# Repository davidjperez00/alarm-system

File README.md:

# alarm-system

## Host Machine Setup

### WSL Install
1. Open powershell as administrator and run (Project Version):
```wsl --intall```

### WSL Connect Serial Ports From Windows
1. When we setup esp idf project build system we will have to connect our Windows usb serial ports to our WSL operation system.
```winget install usbipd ```
2. RESTART your pc, <b>This is only a one time process</b>, once you set
this up it will connect the port service on all boots?
3. After the reboot, In a Powershell window, connect the windows usb port to a WSL port. <b>You will need to do this every reboot</b>. 
</r>TODO: consider connecting the port and through windows only? 

In Powershell admin terminal, look for device Connected to Windows machine: 
```
usbipd list
```

5.  Bind port to WSL OS, Example: 7-1
```
usbipd bind --busid <BUSID>
usbipd attach --wsl --busid <BUSID>
```
6. Back in wsl windows you should see new device connected:
```
# New device should appear in list
ls /dev/tty*
```
7. Then, again in WSL terminal Give current user permission to access port: (TODO: might only need to do once.)
```
sudo usermod -a -G dialout $USER
```

### Github SSH Key Setup for WSL
1. In WSL create keys:
```ssh-keygen -t ed25519 -C "your_email@example.com"```
2. Create directory and manage permissions (Optional), replace <ssh_private_key> with private key name from last step.
```
# Create ssh directory
install -d ~/.ssh
chmod 700 ~/.ssh
# Move private key to ssh directory and set permissions
mv <ssh_private_key>
chmod 600 <ssh_private_key>
```
3. Start ssh agent to add ssh key to working memory (avoids having to specify the key with "ssh -i")
```
# launch ssh-agent
eval "$(ssh-agent -s)"
# Add the key to the agent
ssh-add ~/.ssh/<ssh_private_key>
```

### Required Software Setup 
1. Run the following to install all required software for building this project:
```
./host_dependencies_setup.sh
```

### Building and Running Project
1. Setup esp-idf environemnt variables by running (Only required ONCE when new terminal is opened):
```
source $IDF_PATH/export.sh
```
1. 1 (Optional) Add it to bash profile to load everytime bash terminal window is launched
```
echo "source $IDF_PATH/export.sh" >> ~/.bashrc
```
2. Setting our own ports environment variables?
```
TODO: implemement and test this:
export IDF_TARGET=esp32
export ESPPORT=
export ESPBAUD=
```

3. Building from <b>Src/blink</b>
```
idf.py build
```

4. 

5. Flashing to Device
```
idf.py flash 
```

# Improving Build Speed

## 1. Removing unused config

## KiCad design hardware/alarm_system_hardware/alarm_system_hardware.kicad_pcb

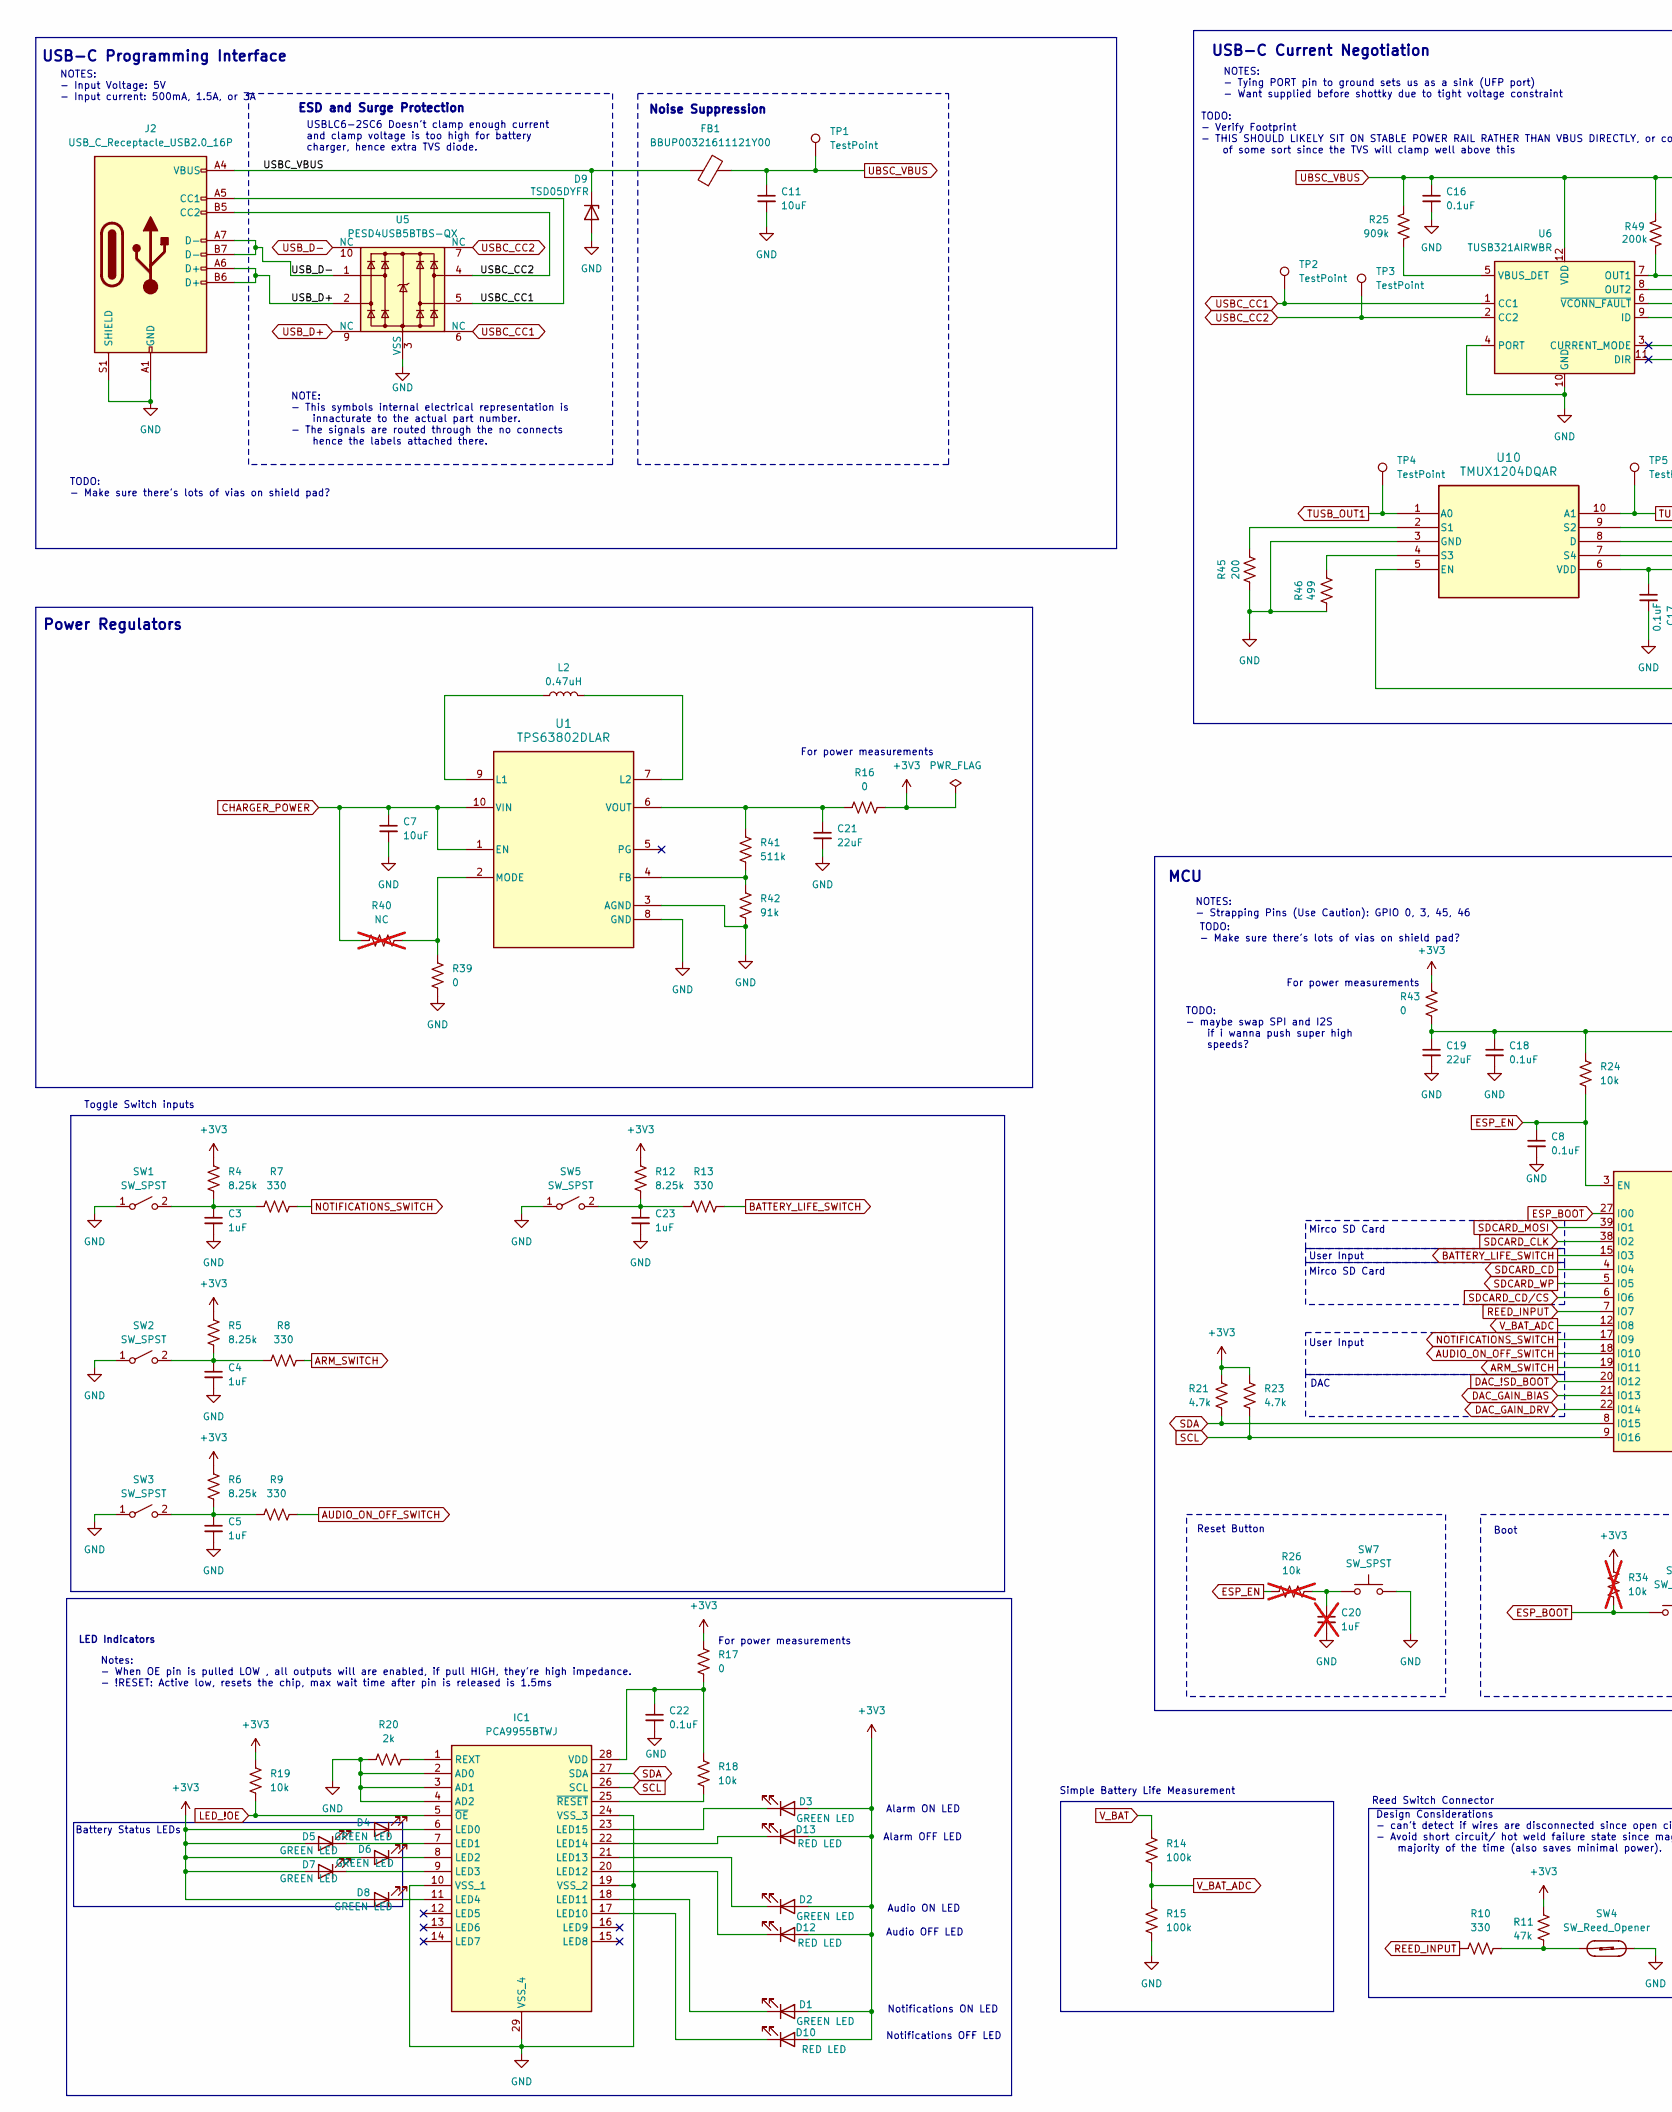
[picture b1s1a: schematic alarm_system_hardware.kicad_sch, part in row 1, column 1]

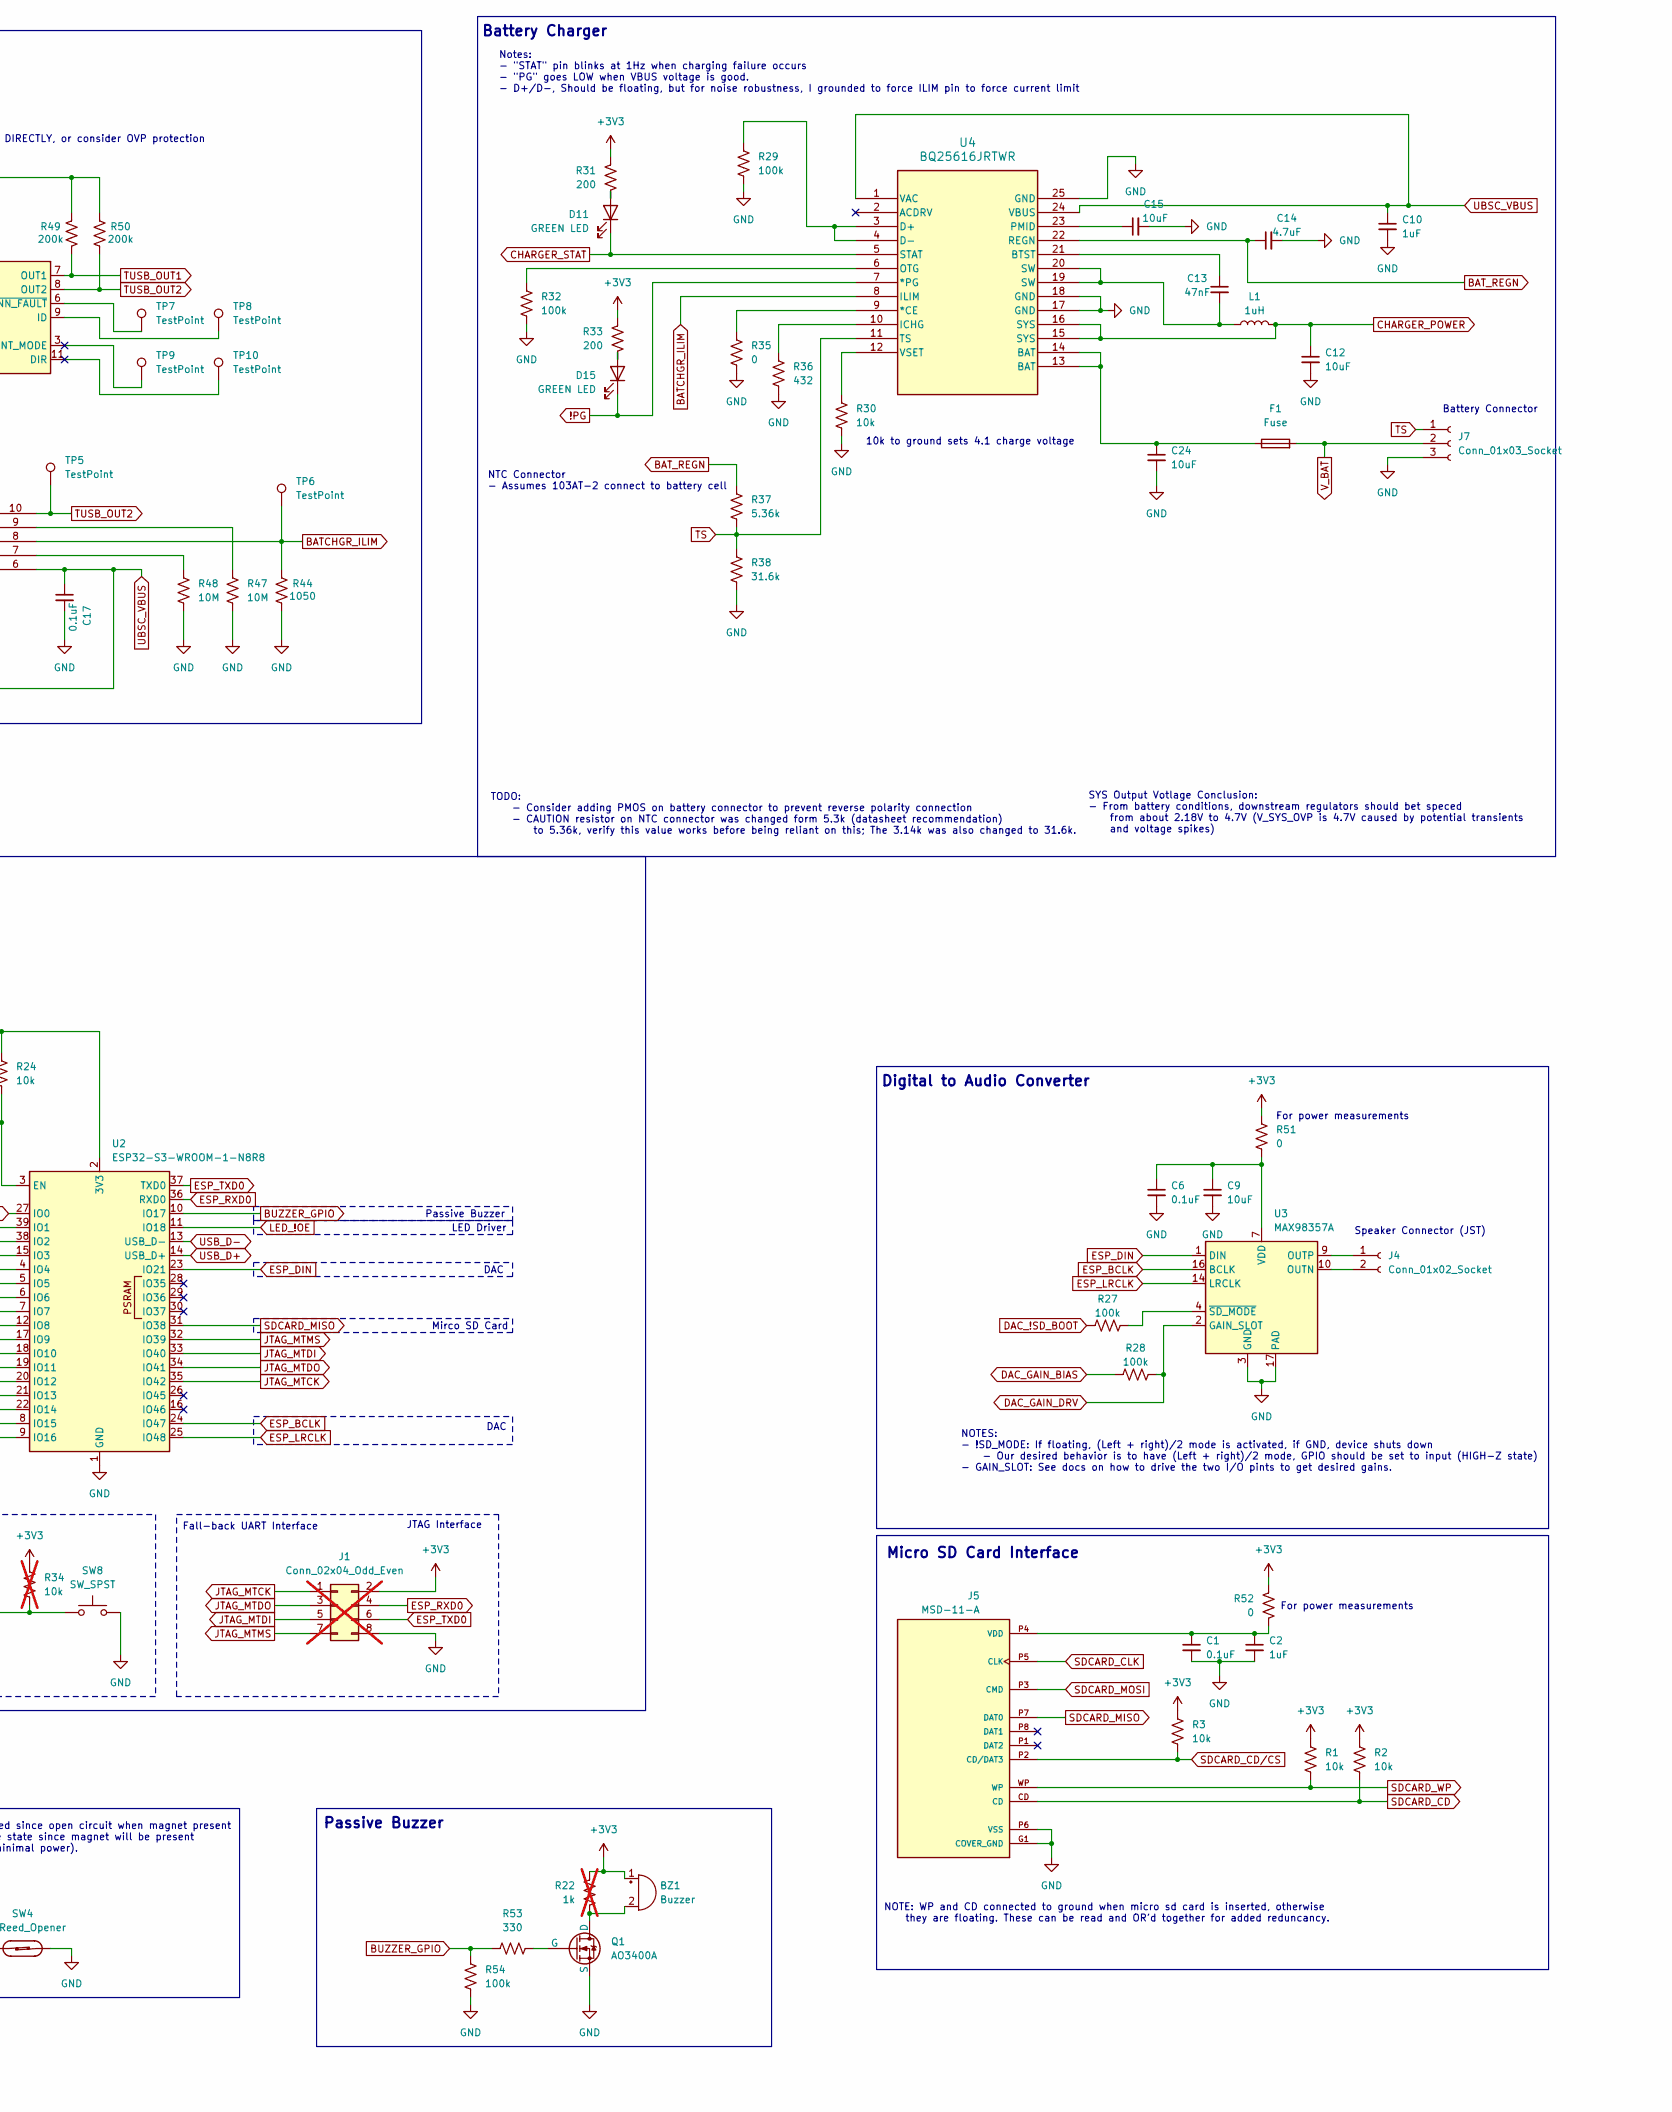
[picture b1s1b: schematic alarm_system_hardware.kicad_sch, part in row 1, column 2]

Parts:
BZ1: Buzzer; PS1440P02BT_TDK; Manufacturer_Part_Number PS1440P02BT
C1, C6, C8, C16, C17, C18, C22: 0.1uF; C_0805_2012Metric_Pad1.18x1.45mm_HandSolder; Manufacturer_Part_Number CC0805KRX7R9BB104
C2, C3, C4, C5, C10, C23: 1uF; C_0805_2012Metric_Pad1.18x1.45mm_HandSolder; Manufacturer_Part_Number GRM21BR71C105KA01L
C7, C9, C11, C12, C15, C24: 10uF; C_0805_2012Metric_Pad1.18x1.45mm_HandSolder; Manufacturer_Part_Number GRM21BR71A106KA73L
C13: 47nF; C_0805_2012Metric_Pad1.18x1.45mm_HandSolder; Manufacturer_Part_Number CL21B473KBCNNNC
C14: 4.7uF; C_0805_2012Metric_Pad1.18x1.45mm_HandSolder; Manufacturer_Part_Number CL21B473KBCNNNC
C19, C21: 22uF; C_0805_2012Metric_Pad1.18x1.45mm_HandSolder; Manufacturer_Part_Number GRM21BZ71A226ME15L
C20: 1uF; C_0805_2012Metric_Pad1.18x1.45mm_HandSolder; Manufacturer_Part_Number GRM21BR71C105KA01L; not fitted
D1, D2, D3, D4, D5, D6, D7, D8, D11, D15: GREEN LED; LED_0805_2012Metric; Manufacturer_Part_Number LTST-C171KGKT
D9: TSD05DYFR; D_SOD-323_HandSoldering; Manufacturer_Part_Number TSD05DYFR
D10, D12, D13: RED LED; LED_0805_2012Metric; Manufacturer_Part_Number LTST-C171KRKT
F1: Fuse; Fuse_0805_2012Metric; Manufacturer_Part_Number MFU0805FF03000P500
FB1: BBUP00321611121Y00; R_1206_3216Metric_Pad1.30x1.75mm_HandSolder; Manufacturer_Part_Number BBUP00321611121Y00
IC1: PCA9955BTWJ; SOP65P640X110-29N; Manufacturer_Part_Number PCA9955BTWJ; Mouser Part Number 771-PCA9955BTW
J1: Conn_02x04_Odd_Even; PinHeader_2x04_P2.54mm_Vertical; not fitted
J2: USB_C_Receptacle_USB2.0_16P; SAMESKY_UJ20-C-H-G-SMT-1-P16-TR; Manufacturer_Part_Number UJ20-C-H-G-SMT-1-P16-TR
J4: Conn_01x02_Socket; CONN_S2B-PH-K-S_JST; Manufacturer_Part_Number S2B-PH-K-S
J5: MSD-11-A; CUI_MSD-11-A; PARTREV 1.02; DigiKey_Part_Number 2223-MSD-11-ACT-ND
J7: Conn_01x03_Socket; TerminalBlock_Phoenix_PT-1,5-3-5.0-H_1x03_P5.00mm_Horizontal; Manufacturer_Part_Number 1935174
L1: 1uH; IND_VLS5045EX-1R0N; Manufacturer_Part_Number VLS5045EX-1R0N
L2: 0.47uH; IND_IHLP-2020CZ-L; Manufacturer_Part_Number IHLP2020CZERR47M11; LCSC Part # C5298158
Q1: AO3400A; SOT-23-3; Manufacturer_Part_Number AO3400A
R1, R2, R3, R18, R19, R24, R30: 10k; R_0805_2012Metric_Pad1.20x1.40mm_HandSolder; Manufacturer_Part_Number RMCF0805FT10K0
R4, R5, R6, R12: 8.25k; R_0805_2012Metric_Pad1.20x1.40mm_HandSolder; Manufacturer_Part_Number RT0805BRD078K25L
R7, R8, R9, R10, R13, R53: 330; R_0805_2012Metric_Pad1.20x1.40mm_HandSolder; Manufacturer_Part_Number RC0805JR-07330RL
R11: 47k; R_0805_2012Metric_Pad1.20x1.40mm_HandSolder; Manufacturer_Part_Number RC0805FR-0747KL
R14, R15, R27, R28, R29, R32, R54: 100k; R_0805_2012Metric_Pad1.20x1.40mm_HandSolder; Manufacturer_Part_Number RC0805FR-07100KL
R16, R17, R35, R39, R43, R51, R52: 0; R_0805_2012Metric_Pad1.20x1.40mm_HandSolder; Manufacturer_Part_Number RC0805JR-070RL
R20: 2k; R_0805_2012Metric_Pad1.20x1.40mm_HandSolder; Manufacturer_Part_Number RC0805FR-072KL
R21, R23: 4.7k; R_0805_2012Metric_Pad1.20x1.40mm_HandSolder; Manufacturer_Part_Number RC0805FR-074K7L
R22: 1k; R_0805_2012Metric_Pad1.20x1.40mm_HandSolder; not fitted
R25: 909k; R_0805_2012Metric_Pad1.20x1.40mm_HandSolder; Manufacturer_Part_Number RC0805FR-07909KL
R26, R34: 10k; R_0805_2012Metric_Pad1.20x1.40mm_HandSolder; Manufacturer_Part_Number RMCF0805FT10K0; not fitted
R31, R33, R45: 200; R_0805_2012Metric_Pad1.20x1.40mm_HandSolder; Manufacturer_Part_Number RC0805FR-07200RL
R36: 432; R_0805_2012Metric_Pad1.20x1.40mm_HandSolder; Manufacturer_Part_Number RC0805FR-07432RL
R37: 5.36k; R_0805_2012Metric_Pad1.20x1.40mm_HandSolder; Manufacturer_Part_Number CRCW08055K36FKEA
R38: 31.6k; R_0805_2012Metric_Pad1.20x1.40mm_HandSolder; Manufacturer_Part_Number RC0805FR-0731K6L
R40: NC; R_0805_2012Metric_Pad1.20x1.40mm_HandSolder; not fitted
R41: 511k; R_0805_2012Metric_Pad1.20x1.40mm_HandSolder; Manufacturer_Part_Number RC0805FR-07511KL
R42: 91k; R_0805_2012Metric_Pad1.20x1.40mm_HandSolder; Manufacturer_Part_Number RC0805FR-0791KL
R44: 1050; R_0805_2012Metric_Pad1.20x1.40mm_HandSolder; Manufacturer_Part_Number RC0805FR-071K05L
R46: 499; R_0805_2012Metric_Pad1.20x1.40mm_HandSolder; Manufacturer_Part_Number RC0805FR-07499RL
R47, R48: 10M; R_0805_2012Metric_Pad1.20x1.40mm_HandSolder; Manufacturer_Part_Number RC0805FR-0710ML
R49, R50: 200k; R_0805_2012Metric_Pad1.20x1.40mm_HandSolder; Manufacturer_Part_Number RC0805FR-07200KL
SW1, SW2, SW3, SW5, SW7, SW8: SW_SPST; SW_SPST_CK_RS282G05A3; Manufacturer_Part_Number PTS636SK25FSMTR LFS
SW4: SW_Reed_Opener; TerminalBlock_Phoenix_PT-1,5-2-5.0-H_1x02_P5.00mm_Horizontal; Manufacturer_Part_Number 1935161
TP1, TP2, TP3, TP4, TP5, TP6, TP7, TP8, TP9, TP10: TestPoint; TestPoint_Pad_D1.0mm
U1: TPS63802DLAR; DLA0010A; Manufacturer_Part_Number TPS63802DLAR
U2: ESP32-S3-WROOM-1-N8R8; ESP32-S3-WROOM-1; Manufacturer_Part_Number ESP32-S3-WROOM-1-N8R8
U3: MAX98357A; TQFN-16-1EP_3x3mm_P0.5mm_EP1.23x1.23mm; Manufacturer_Part_Number MAX98357AETE+T
U4: BQ25616JRTWR; WQFN24_RTW_TEX; Manufacturer_Part_Number BQ25616RTWR
U5: PESD4USB5BTBS-QX; Diodes_UDFN-10_1.0x2.5mm_P0.5mm; Manufacturer_Part_Number PESD4USB5BTBS-QX
U6: TUSB321AIRWBR; Texas_X2QFN-12_1.6x1.6mm_P0.4mm; Manufacturer_Part_Number TUSB321AIRWBR
U10: TMUX1204DQAR; USON10_DQA_TEX; Manufacturer_Part_Number TMUX1204DQAR

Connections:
!PG: D15.1 (K), U4.7 (*PG)
+3V3: BZ1.1 (+), D1.2 (A), D2.2 (A), D3.2 (A), D4.2 (A), D5.2 (A), D6.2 (A), D7.2 (A), D8.2 (A), D10.2 (A), D12.2 (A), D13.2 (A), J1.2, R1.1, R2.1, R3.1, R4.1, R5.1, R6.1, R11.1, R12.1, R16.2, R17.2, R19.1, R21.1, R22.1, R23.1, R31.1, R33.1, R34.1, R43.2, R51.2, R52.2
/USBC_VBUS: D9.1 (K), FB1.1, J2.A4 (VBUS), J2.A9 (VBUS), J2.B4 (VBUS), J2.B9 (VBUS)
ARM_SWITCH: R8.2, U2.19 (IO11)
AUDIO_ON_OFF_SWITCH: R9.2, U2.18 (IO10)
BATCHGR_ILIM: R44.1, TP6.1, U4.8 (ILIM), U10.8 (D)
BATTERY_LIFE_SWITCH: R13.2, U2.15 (IO3)
BAT_REGN: C14.1, R37.1, U4.22 (REGN)
BUZZER_GPIO: R53.2, R54.1, U2.10 (IO17)
CHARGER_POWER: C7.1, C12.1, L1.2, R40.1, U1.1 (EN), U1.10 (VIN), U4.15 (SYS), U4.16 (SYS)
CHARGER_STAT: D11.1 (K), U4.5 (STAT)
DAC_!SD_BOOT: R27.1, U2.20 (IO12)
DAC_GAIN_BIAS: R28.1, U2.21 (IO13)
DAC_GAIN_DRV: R28.2, U2.22 (IO14), U3.2 (GAIN_SLOT)
ESP_BCLK: U2.24 (IO47), U3.16 (BCLK)
ESP_BOOT: R34.2, SW8.1, U2.27 (IO0)
ESP_DIN: U2.23 (IO21), U3.1 (DIN)
ESP_EN: C8.1, R24.2, R26.1, U2.3 (EN)
ESP_LRCLK: U2.25 (IO48), U3.14 (LRCLK)
ESP_RXD0: J1.4, U2.36 (RXD0)
ESP_TXD0: J1.6, U2.37 (TXD0)
GND: C1.2, C2.2, C3.2, C4.2, C5.2, C6.2, C7.2, C8.2, C9.2, C10.2, C11.2, C12.2, C14.2, C15.2, C16.2, C17.2, C18.2, C19.2, C20.2, C21.2, C22.2, C23.2, C24.2, D9.2 (A), IC1.2 (AD0), IC1.3 (AD1), IC1.4 (AD2), IC1.10 (VSS_1), IC1.19 (VSS_2), IC1.24 (VSS_3), IC1.29 (VSS_4), J1.8, J2.A1 (GND), J2.A12 (GND), J2.B1 (GND), J2.B12 (GND), J2.S1 (SHIELD), J5.G1 (COVER_GND), J5.G2 (COVER_GND), J5.P6 (VSS), J7.3, Q1.3 (S), R15.2, R20.1, R29.2, R30.2, R32.2, R35.2, R36.2, R38.2, R39.2, R42.2, R44.2, R45.1, R46.1, R47.2, R48.2, R54.2, SW1.1 (A), SW2.1 (A), SW3.1 (A), SW4.2, SW5.1 (A), SW7.2, SW8.2, U1.3 (AGND), U1.8 (GND), U2.1 (GND), U2.40 (GND), U2.41 (GND), U3.3 (GND), U3.11 (GND), U3.15 (GND), U3.17 (PAD), U4.17 (GND), U4.18 (GND), U4.25 (GND), U5.3 (VSS), U5.8 (VSS), U6.4 (PORT), U6.10 (GND), U10.3 (GND)
JTAG_MTCK: J1.1, U2.35 (IO42)
JTAG_MTDI: J1.5, U2.33 (IO40)
JTAG_MTDO: J1.3, U2.34 (IO41)
JTAG_MTMS: J1.7, U2.32 (IO39)
LED_!OE: IC1.5 (~OE), R19.2, U2.11 (IO18)
NOTIFICATIONS_SWITCH: R7.2, U2.17 (IO9)
unnamed: BZ1.2 (-), Q1.1 (D), R22.2
unnamed: C6.1, C9.1, R51.1, U3.7 (VDD), U3.8 (VDD)
unnamed: C13.2, L1.1, U4.19 (SW), U4.20 (SW)
unnamed: C20.1, R26.2, SW7.1
unnamed: C24.1, F1.1, U4.13 (BAT), U4.14 (BAT)
unnamed: D1.1 (K), IC1.18 (LED11)
unnamed: D2.1 (K), IC1.21 (LED13)
unnamed: D3.1 (K), IC1.23 (LED15)
unnamed: D4.1 (K), IC1.6 (LED0)
unnamed: D5.1 (K), IC1.7 (LED1)
unnamed: D6.1 (K), IC1.8 (LED2)
unnamed: D7.1 (K), IC1.9 (LED3)
unnamed: D8.1 (K), IC1.11 (LED4)
unnamed: D10.1 (K), IC1.17 (LED10)
unnamed: D11.2 (A), R31.2
unnamed: D12.1 (K), IC1.20 (LED12)
unnamed: D13.1 (K), IC1.22 (LED14)
unnamed: D15.2 (A), R33.2
unnamed: IC1.1 (REXT), R20.2
unnamed: C22.1, IC1.28 (VDD), R17.1, R18.1
unnamed: IC1.25 (~RESET), R18.2
unnamed: J4.1, U3.9 (OUTP)
unnamed: J4.2, U3.10 (OUTN)
unnamed: C1.1, C2.1, J5.P4 (VDD), R52.1
unnamed: Q1.2 (G), R53.1
unnamed: R10.2, R11.2, SW4.1
unnamed: C3.1, R4.2, R7.1, SW1.2 (B)
unnamed: C4.1, R5.2, R8.1, SW2.2 (B)
unnamed: C5.1, R6.2, R9.1, SW3.2 (B)
unnamed: C23.1, R12.2, R13.1, SW5.2 (B)
unnamed: R41.2, R42.1, U1.4 (FB)
unnamed: L2.1, U1.9 (L1)
unnamed: L2.2, U1.7 (L2)
unnamed: R39.1, R40.2, U1.2 (MODE)
unnamed: C21.1, R16.1, R41.1, U1.6 (VOUT)
unnamed: C18.1, C19.1, R24.1, R43.1, U2.2 (3V3)
unnamed: R27.2, U3.4 (~SD_MODE)
unnamed: R35.1, U4.9 (*CE)
unnamed: C13.1, U4.21 (BTST)
unnamed: R29.1, U4.3 (D+), U4.4 (D-)
unnamed: R36.1, U4.10 (ICHG)
unnamed: R32.1, U4.6 (OTG)
unnamed: C15.1, U4.23 (PMID)
unnamed: R30.1, U4.12 (VSET)
unnamed: TP8.1, U6.9 (ID)
unnamed: R25.2, U6.5 (VBUS_DET)
unnamed: TP7.1, U6.6 (~VCONN_FAULT)
unnamed: R45.2, U10.2 (S1)
unnamed: R47.1, U10.9 (S2)
unnamed: R46.2, U10.4 (S3)
unnamed: R48.1, U10.7 (S4)
REED_INPUT: R10.1, U2.7 (IO7)
SCL: IC1.26 (SCL), R23.2, U2.9 (IO16)
SDA: IC1.27 (SDA), R21.2, U2.8 (IO15)
SDCARD_CD: J5.CD, R2.2, U2.4 (IO4)
SDCARD_CD/CS: J5.P2 (CD/DAT3), R3.2, U2.6 (IO6)
SDCARD_CLK: J5.P5 (CLK), U2.38 (IO2)
SDCARD_MISO: J5.P7 (DAT0), U2.31 (IO38)
SDCARD_MOSI: J5.P3 (CMD), U2.39 (IO1)
SDCARD_WP: J5.WP, R1.2, U2.5 (IO5)
TS: J7.1, R37.2, R38.1, U4.11 (TS)
TUSB_OUT1: R49.2, TP4.1, U6.7 (OUT1), U10.1 (A0)
TUSB_OUT2: R50.2, TP5.1, U6.8 (OUT2), U10.10 (A1)
UBSC_VBUS: C10.1, C11.1, C16.1, C17.1, FB1.2, R25.1, R49.1, R50.1, TP1.1, U4.1 (VAC), U4.24 (VBUS), U6.12 (VDD), U10.5 (EN), U10.6 (VDD)
USBC_CC1: J2.A5 (CC1), TP2.1, U5.5, U5.6 (NC), U6.1 (CC1)
USBC_CC2: J2.B5 (CC2), TP3.1, U5.4, U5.7 (NC), U6.2 (CC2)
USB_D+: J2.A6 (D+), J2.B6 (D+), U2.14 (USB_D+), U5.2, U5.9 (NC)
USB_D-: J2.A7 (D-), J2.B7 (D-), U2.13 (USB_D-), U5.1, U5.10 (NC)
V_BAT: F1.2, J7.2, R14.1
V_BAT_ADC: R14.2, R15.1, U2.12 (IO8)

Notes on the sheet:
TODO: - maybe swap SPI and I2S if i wanna push super high speeds?
Toggle Switch inputs
For power measurements
10k to ground sets 4.1 charge voltage
Notes: - "STAT" pin blinks at 1Hz when charging failure occurs - "PG" goes LOW when VBUS voltage is good. - D+/D-, Should be floating, but for noise robustness, I grounded to force ILIM pin to force current limit
Notifications ON LED
Design Considerations - can't detect if wires are disconnected since open circuit when magnet present - Avoid short circuit/ hot weld failure state since magnet will be present majority of the time (also saves minimal power).
LED Driver
DAC
NOTES: - Input Voltage: 5V - Input current: 500mA, 1.5A, or 3A
NOTES: - Strapping Pins (Use Caution): GPIO 0, 3, 45, 46
Battery Connector
Mirco SD Card
Micro SD Card Interface
Alarm OFF LED
Noise Suppression
USB-C Programming Interface
Fall-back UART Interface
User Input
Notes: - When OE pin is pulled LOW , all outputs will are enabled, if pull HIGH, they're high impedance. - !RESET: Active low, resets the chip, max wait time after pin is released is 1.5ms
USB-C Current Negotiation
USBLC6-2SC6 Doesn't clamp enough current and clamp voltage is too high for battery charger, hence extra TVS diode.
LED Indicators
NOTES: - !SD_MODE: If floating, (Left + right)/2 mode is activated, if GND, device shuts down - Our desired behavior is to have (Left + right)/2 mode, GPIO should be set to input (HIGH-Z state) - GAIN_SLOT: See docs on how to drive the two I/O pints to get desired gains.
Audio ON LED
NOTES: - Tying PORT pin to ground sets us as a sink (UFP port) - Want supplied before shottky due to tight voltage constraint
JTAG Interface
Boot
MCU
ESD and Surge Protection
Battery Charger
Reset Button
Passive Buzzer
Power Regulators
SYS Output Votlage Conclusion: - From battery conditions, downstream regulators should bet speced from about 2.18V to 4.7V (V_SYS_OVP is 4.7V caused by potential transients and voltage spikes)
Reed Switch Connector
TODO: - Consider adding PMOS on battery connector to prevent reverse polarity connection - CAUTION resistor on NTC connector was changed form 5.3k (datasheet recommendation) to 5.36k, verify this value works before being reliant on this; The 3.14k was also changed to 31.6k.
NOTE: WP and CD connected to ground when micro sd card is inserted, otherwise they are floating. These can be read and OR'd together for added reduncancy.
Simple Battery Life Measurement
NTC Connector - Assumes 103AT-2 connect to battery cell

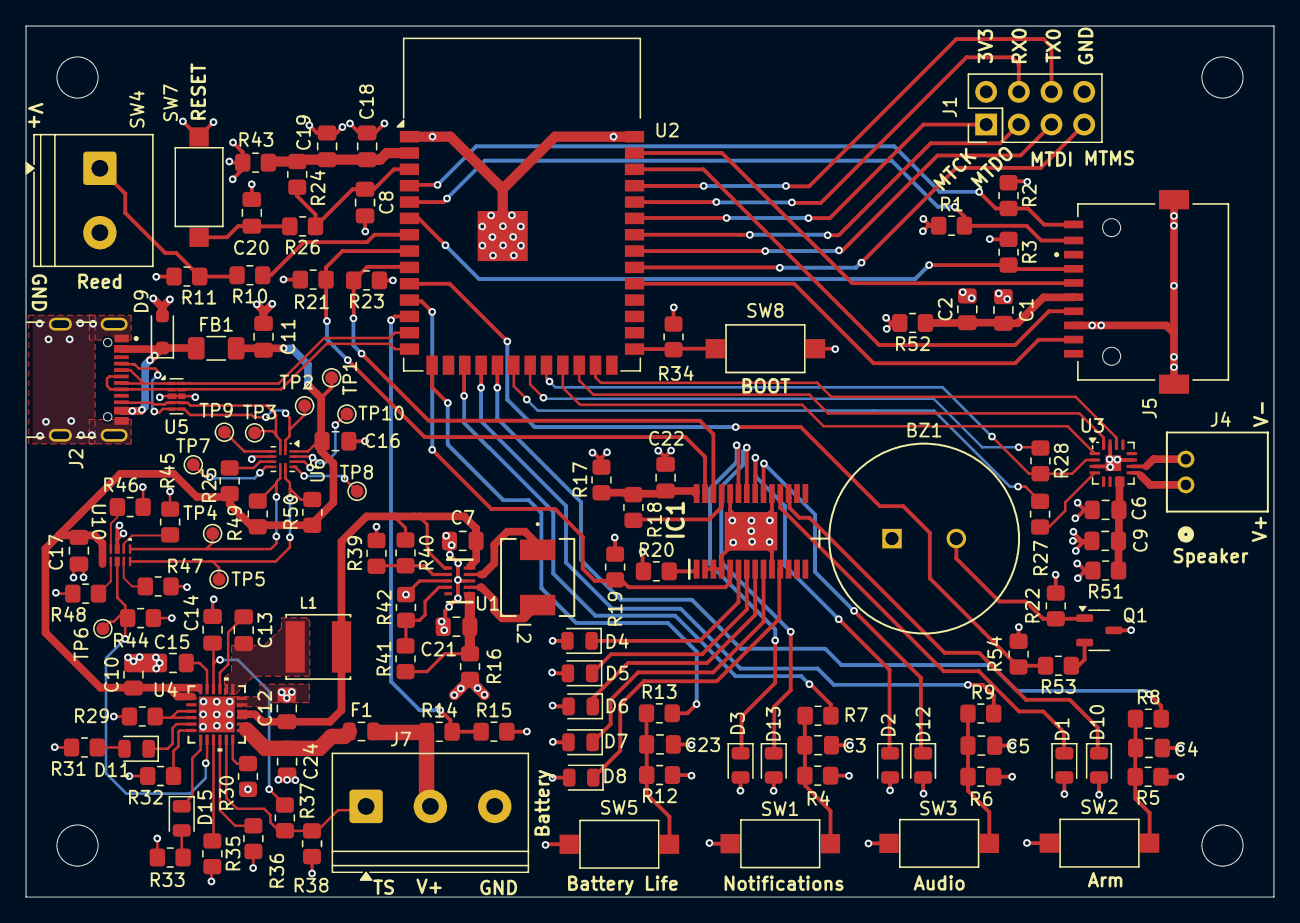
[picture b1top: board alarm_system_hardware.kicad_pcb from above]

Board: 4 copper layers, 97.0 x 67.7 mm, 128 parts (0 on the bottom side), 98 nets.

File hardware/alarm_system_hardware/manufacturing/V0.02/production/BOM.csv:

"Designator","Footprint","Qty","Comment","Manufacturer_Name","Manufacturer_Part_Number","LCSC Part #"
"BZ1","alarm_system:PS1440P02BT_TDK","1","Buzzer","TDK","PS1440P02BT",""
"C1,C6,C8,C16,C17,C18,C22","Capacitor_SMD:C_0805_2012Metric_Pad1.18x1.45mm_HandSolder","7","0.1uF","YAGEO","CC0805KRX7R9BB104",""
"C2,C3,C4,C5,C10,C23","Capacitor_SMD:C_0805_2012Metric_Pad1.18x1.45mm_HandSolder","6","1uF","Murata Electronics","GRM21BR71C105KA01L",""
"C7,C9,C11,C12,C15,C24","Capacitor_SMD:C_0805_2012Metric_Pad1.18x1.45mm_HandSolder","6","10uF","Murata Electronics","GRM21BR71A106KA73L",""
"C13","Capacitor_SMD:C_0805_2012Metric_Pad1.18x1.45mm_HandSolder","1","47nF","Samsung Electro-Mechanics","CL21B473KBCNNNC",""
"C14","Capacitor_SMD:C_0805_2012Metric_Pad1.18x1.45mm_HandSolder","1","4.7uF","Samsung Electro-Mechanics","CL21B473KBCNNNC",""
"C19,C21","Capacitor_SMD:C_0805_2012Metric_Pad1.18x1.45mm_HandSolder","2","22uF","Murata Electronics","GRM21BZ71A226ME15L",""
"D1,D2,D3,D4,D5,D6,D7,D8,D11,D15","LED_SMD:LED_0805_2012Metric","10","GREEN LED","Lite-On Inc.","LTST-C171KGKT",""
"D9","Diode_SMD:D_SOD-323_HandSoldering","1","TSD05DYFR","Texas Instruments","TSD05DYFR",""
"D10,D12,D13","LED_SMD:LED_0805_2012Metric","3","RED LED","Lite-On Inc.","LTST-C171KRKT",""
"F1","Fuse:Fuse_0805_2012Metric","1","Fuse","Vishay","MFU0805FF03000P100",""
"FB1","Resistor_SMD:R_1206_3216Metric_Pad1.30x1.75mm_HandSolder","1","BBUP00321611121Y00","Pulse Electronics","BBUP00321611121Y00",""
"IC1","SOP65P640X110-29N","1","PCA9955BTWJ","NXP USA Inc.","PCA9955BTWJ",""
"J2","alarm_system:SAMESKY_UJ20-C-H-G-SMT-1-P16-TR","1","USB_C_Receptacle_USB2.0_16P","Same Sky (Formerly CUI Devices)","UJ20-C-H-G-SMT-1-P16-TR",""
"J4","alarm_system:CONN_S2B-PH-K-S_JST","1","Conn_01x02_Socket","JST Sales America Inc.","S2B-PH-K-S",""
"J5","alarm_system:CUI_MSD-11-A","1","MSD-11-A","Same Sky (Formerly CUI Devices)","MSD-11-A",""
"J7","TerminalBlock_Phoenix:TerminalBlock_Phoenix_PT-1,5-3-5.0-H_1x03_P5.00mm_Horizontal","1","Conn_01x03_Socket","Phoenix Contact","1935174",""
"L1","alarm_system:IND_VLS5045EX-1R0N","1","1uH","TDK","VLS5045EX-1R0N",""
"L2","alarm_system:IND_IHLP-2020CZ-L","1","0.47uH","Vishay Dale","IHLP2020CZERR47M11",""
"Q1","Package_TO_SOT_SMD:SOT-23-3","1","AO3400A","Alpha & Omega Semiconductor Inc.","AO3400A",""
"R1,R2,R3,R18,R19,R24,R30","Resistor_SMD:R_0805_2012Metric_Pad1.20x1.40mm_HandSolder","7","10k","Stackpole Electronics Inc","RMCF0805FT10K0",""
"R4,R5,R6,R12","Resistor_SMD:R_0805_2012Metric_Pad1.20x1.40mm_HandSolder","4","8.25k","YAGEO","RT0805BRD078K25L",""
"R7,R8,R9,R10,R13,R53","Resistor_SMD:R_0805_2012Metric_Pad1.20x1.40mm_HandSolder","6","330","YAGEO","RC0805JR-07330RL",""
"R11","Resistor_SMD:R_0805_2012Metric_Pad1.20x1.40mm_HandSolder","1","47k","YAGEO","RC0805FR-0747KL",""
"R14,R15,R27,R28,R29,R32,R54","Resistor_SMD:R_0805_2012Metric_Pad1.20x1.40mm_HandSolder","7","100k","YAGEO","RC0805FR-07100KL",""
"R16,R17,R35,R39,R43,R51,R52","Resistor_SMD:R_0805_2012Metric_Pad1.20x1.40mm_HandSolder","7","0","YAGEO","RC0805JR-070RL",""
"R20","Resistor_SMD:R_0805_2012Metric_Pad1.20x1.40mm_HandSolder","1","2k","YAGEO","RC0805FR-072KL",""
"R21,R23","Resistor_SMD:R_0805_2012Metric_Pad1.20x1.40mm_HandSolder","2","4.7k","YAGEO","RC0805FR-074K7L",""
"R25","Resistor_SMD:R_0805_2012Metric_Pad1.20x1.40mm_HandSolder","1","909k","YAGEO","RC0805FR-07909KL",""
"R31,R33,R45","Resistor_SMD:R_0805_2012Metric_Pad1.20x1.40mm_HandSolder","3","200","YAGEO","RC0805FR-07200RL",""
"R36","Resistor_SMD:R_0805_2012Metric_Pad1.20x1.40mm_HandSolder","1","432","YAGEO","RC0805FR-07432RL",""
"R37","Resistor_SMD:R_0805_2012Metric_Pad1.20x1.40mm_HandSolder","1","5.36k","Vishay Dale","CRCW08055K36FKEA",""
"R38","Resistor_SMD:R_0805_2012Metric_Pad1.20x1.40mm_HandSolder","1","31.6k","YAGEO","RC0805FR-0731K6L",""
"R41","Resistor_SMD:R_0805_2012Metric_Pad1.20x1.40mm_HandSolder","1","511k","YAGEO","RC0805FR-07511KL",""
"R42","Resistor_SMD:R_0805_2012Metric_Pad1.20x1.40mm_HandSolder","1","91k","YAGEO","RC0805FR-0791KL",""
"R44","Resistor_SMD:R_0805_2012Metric_Pad1.20x1.40mm_HandSolder","1","1050","YAGEO","RC0805FR-071K05L",""
"R46","Resistor_SMD:R_0805_2012Metric_Pad1.20x1.40mm_HandSolder","1","499","YAGEO","RC0805FR-07499RL",""
"R47,R48","Resistor_SMD:R_0805_2012Metric_Pad1.20x1.40mm_HandSolder","2","10M","YAGEO","RC0805FR-0710ML",""
"R49,R50","Resistor_SMD:R_0805_2012Metric_Pad1.20x1.40mm_HandSolder","2","200k","YAGEO","RC0805FR-07200KL",""
"SW1,SW2,SW3,SW5,SW7,SW8","Button_Switch_SMD:SW_SPST_CK_RS282G05A3","6","SW_SPST","C&K","PTS636SK25FSMTR LFS",""
"SW4","TerminalBlock_Phoenix:TerminalBlock_Phoenix_PT-1,5-2-5.0-H_1x02_P5.00mm_Horizontal","1","SW_Reed_Opener","Phoenix Contact","1935161",""
"U1","DLA0010A","1","TPS63802DLAR","Texas Instruments","TPS63802DLAR",""
"U2","RF_Module:ESP32-S3-WROOM-1","1","ESP32-S3-WROOM-1-N8R8","Espressif Systems","ESP32-S3-WROOM-1-N8R8",""
"U3","Package_DFN_QFN:TQFN-16-1EP_3x3mm_P0.5mm_EP1.23x1.23mm","1","MAX98357A","Analog Devices Inc./Maxim Integrated","MAX98357AETE+T",""
"U4","WQFN24_RTW_TEX","1","BQ25616JRTWR","Texas Instruments","BQ25616JRTWR",""
"U5","Package_DFN_QFN:Diodes_UDFN-10_1.0x2.5mm_P0.5mm","1","PESD4USB5BTBS-QX","Nexperia USA Inc.","PESD4USB5BTBS-QX",""
"U6","Package_DFN_QFN:Texas_X2QFN-12_1.6x1.6mm_P0.4mm","1","TUSB321AIRWBR","Texas Instruments","TUSB321AIRWBR",""
"U10","USON10_DQA_TEX","1","TMUX1204DQAR","Texas Instruments","TMUX1204DQAR",""

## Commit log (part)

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2025-12-07 basic
2025-12-19 Initial i2s testing with esp32 and esp idf
2025-12-20 WIP noisy speaker hum
2025-12-23 Mac system setup and signal testing
2025-12-23 play 440hz for 1 second
2025-12-23 wip structure changes
2025-12-25 new architecture
2025-12-26 updated architecture wip with sin wave
2026-01-10 wip driver testing
2026-01-14 in-progress ring buffer implementation, sin wav test worked prior
2026-01-17 Working audio stream
2026-01-24 heavy code clean up and refactor
2026-01-24 improve robustness of i2s system
2026-03-20 wip initial prototype, need final schematic review
2026-05-15 Add footprints for remaining parts
2026-05-15 remove lock file
